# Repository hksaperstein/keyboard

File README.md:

# keyboard
Creating a custom mechanical keyboard pcb with rgbw backlighting

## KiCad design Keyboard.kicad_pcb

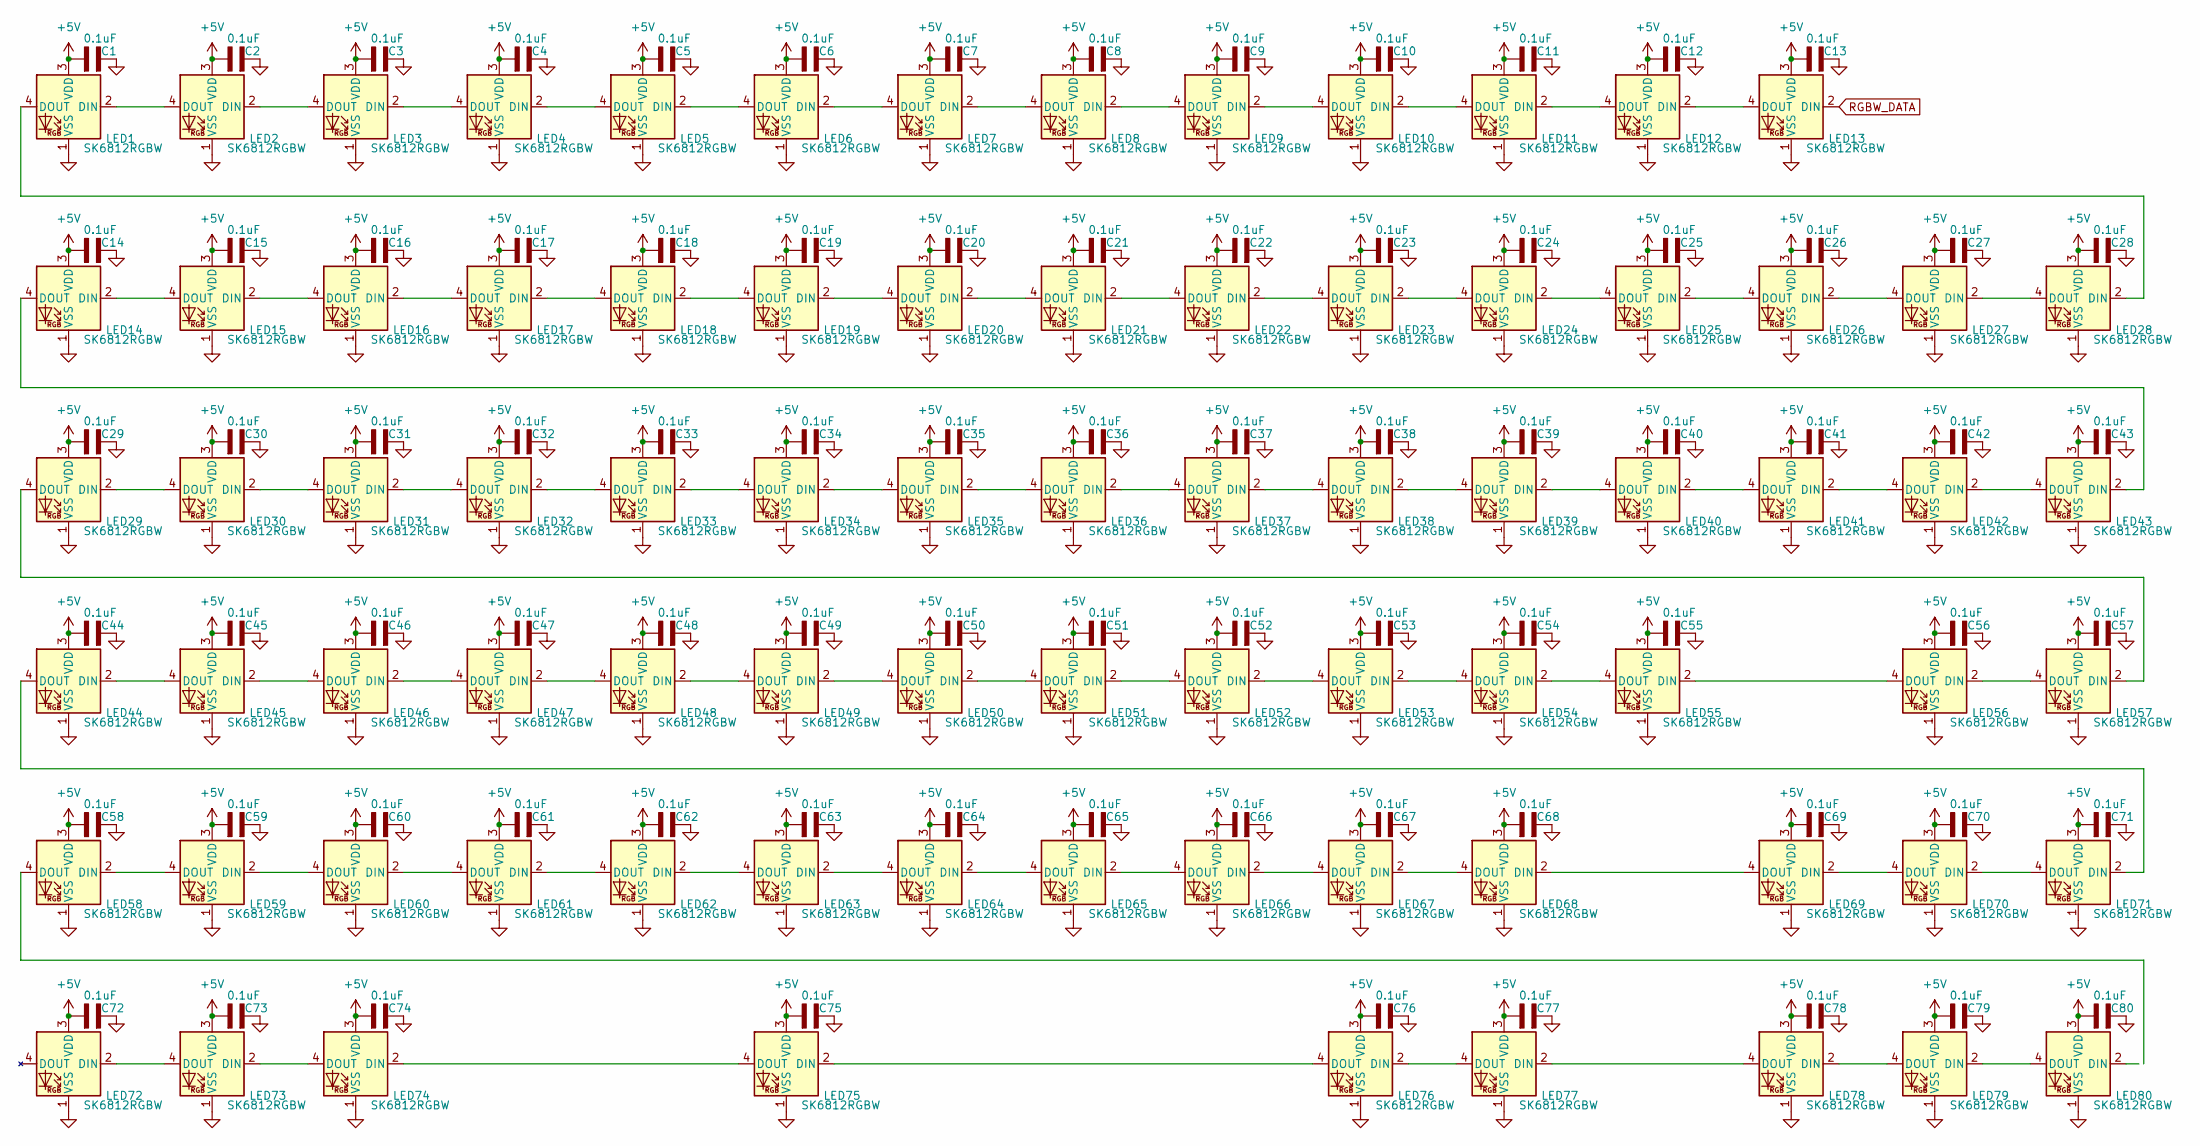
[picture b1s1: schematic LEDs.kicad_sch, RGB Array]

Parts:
C1, C2, C3, C4, C5, C6, C7, C8, C9, C10, C11, C12, C13, C14, C15, C16, C17, C18, C19, C20, C21, C22, C23, C24, C25, C26, C27, C28, C29, C30, C31, C32, C33, C34, C35, C36, C37, C38, C39, C40, C41, C42, C43, C44, C45, C46, C47, C48, C49, C50, C51, C52, C53, C54, C55, C56, C57, C58, C59, C60, C61, C62, C63, C64, C65, C66, C67, C68, C69, C70, C71, C72, C73, C74, C75, C76, C77, C78, C79, C80: 0.1uF; CAPC1608X87N
LED1, LED2, LED3, LED4, LED5, LED6, LED7, LED8, LED9, LED10, LED11, LED12, LED13, LED14, LED15, LED16, LED17, LED18, LED19, LED20, LED21, LED22, LED23, LED24, LED25, LED26, LED27, LED28, LED29, LED30, LED31, LED32, LED33, LED34, LED35, LED36, LED37, LED38, LED39, LED40, LED41, LED42, LED43, LED44, LED45, LED46, LED47, LED48, LED49, LED50, LED51, LED52, LED53, LED54, LED55, LED56, LED57, LED58, LED59, LED60, LED61, LED62, LED63, LED64, LED65, LED66, LED67, LED68, LED69, LED70, LED71, LED72, LED73, LED74, LED75, LED76, LED77, LED78, LED79, LED80: SK6812RGBW; LED_SK6812_PLCC4_5.0x5.0mm_P1.6mm

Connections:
+5V: C1.1, C2.1, C3.1, C4.1, C5.1, C6.1, C7.1, C8.1, C9.1, C10.1, C11.1, C12.1, C13.1, C14.1, C15.1, C16.1, C17.1, C18.1, C19.1, C20.1, C21.1, C22.1, C23.1, C24.1, C25.1, C26.1, C27.1, C28.1, C29.1, C30.1, C31.1, C32.1, C33.1, C34.1, C35.1, C36.1, C37.1, C38.1, C39.1, C40.1, C41.1, C42.1, C43.1, C44.1, C45.1, C46.1, C47.1, C48.1, C49.1, C50.1, C51.1, C52.1, C53.1, C54.1, C55.1, C56.1, C57.1, C58.1, C59.1, C60.1, C61.1, C62.1, C63.1, C64.1, C65.1, C66.1, C67.1, C68.1, C69.1, C70.1, C71.1, C72.1, C73.1, C74.1, C75.1, C76.1, C77.1, C78.1, C79.1, C80.1, LED1.3 (VDD), LED2.3 (VDD), LED3.3 (VDD), LED4.3 (VDD), LED5.3 (VDD), LED6.3 (VDD), LED7.3 (VDD), LED8.3 (VDD), LED9.3 (VDD), LED10.3 (VDD), LED11.3 (VDD), LED12.3 (VDD), LED13.3 (VDD), LED14.3 (VDD), LED15.3 (VDD), LED16.3 (VDD), LED17.3 (VDD), LED18.3 (VDD), LED19.3 (VDD), LED20.3 (VDD), LED21.3 (VDD), LED22.3 (VDD), LED23.3 (VDD), LED24.3 (VDD), LED25.3 (VDD), LED26.3 (VDD), LED27.3 (VDD), LED28.3 (VDD), LED29.3 (VDD), LED30.3 (VDD), LED31.3 (VDD), LED32.3 (VDD), LED33.3 (VDD), LED34.3 (VDD), LED35.3 (VDD), LED36.3 (VDD), LED37.3 (VDD), LED38.3 (VDD), LED39.3 (VDD), LED40.3 (VDD), LED41.3 (VDD), LED42.3 (VDD), LED43.3 (VDD), LED44.3 (VDD), LED45.3 (VDD), LED46.3 (VDD), LED47.3 (VDD), LED48.3 (VDD), LED49.3 (VDD), LED50.3 (VDD), LED51.3 (VDD), LED52.3 (VDD), LED53.3 (VDD), LED54.3 (VDD), LED55.3 (VDD), LED56.3 (VDD), LED57.3 (VDD), LED58.3 (VDD), LED59.3 (VDD), LED60.3 (VDD), LED61.3 (VDD), LED62.3 (VDD), LED63.3 (VDD), LED64.3 (VDD), LED65.3 (VDD), LED66.3 (VDD), LED67.3 (VDD), LED68.3 (VDD), LED69.3 (VDD), LED70.3 (VDD), LED71.3 (VDD), LED72.3 (VDD), LED73.3 (VDD), LED74.3 (VDD), LED75.3 (VDD), LED76.3 (VDD), LED77.3 (VDD), LED78.3 (VDD), LED79.3 (VDD), LED80.3 (VDD)
GND: C1.2, C2.2, C3.2, C4.2, C5.2, C6.2, C7.2, C8.2, C9.2, C10.2, C11.2, C12.2, C13.2, C14.2, C15.2, C16.2, C17.2, C18.2, C19.2, C20.2, C21.2, C22.2, C23.2, C24.2, C25.2, C26.2, C27.2, C28.2, C29.2, C30.2, C31.2, C32.2, C33.2, C34.2, C35.2, C36.2, C37.2, C38.2, C39.2, C40.2, C41.2, C42.2, C43.2, C44.2, C45.2, C46.2, C47.2, C48.2, C49.2, C50.2, C51.2, C52.2, C53.2, C54.2, C55.2, C56.2, C57.2, C58.2, C59.2, C60.2, C61.2, C62.2, C63.2, C64.2, C65.2, C66.2, C67.2, C68.2, C69.2, C70.2, C71.2, C72.2, C73.2, C74.2, C75.2, C76.2, C77.2, C78.2, C79.2, C80.2, LED1.1 (VSS), LED2.1 (VSS), LED3.1 (VSS), LED4.1 (VSS), LED5.1 (VSS), LED6.1 (VSS), LED7.1 (VSS), LED8.1 (VSS), LED9.1 (VSS), LED10.1 (VSS), LED11.1 (VSS), LED12.1 (VSS), LED13.1 (VSS), LED14.1 (VSS), LED15.1 (VSS), LED16.1 (VSS), LED17.1 (VSS), LED18.1 (VSS), LED19.1 (VSS), LED20.1 (VSS), LED21.1 (VSS), LED22.1 (VSS), LED23.1 (VSS), LED24.1 (VSS), LED25.1 (VSS), LED26.1 (VSS), LED27.1 (VSS), LED28.1 (VSS), LED29.1 (VSS), LED30.1 (VSS), LED31.1 (VSS), LED32.1 (VSS), LED33.1 (VSS), LED34.1 (VSS), LED35.1 (VSS), LED36.1 (VSS), LED37.1 (VSS), LED38.1 (VSS), LED39.1 (VSS), LED40.1 (VSS), LED41.1 (VSS), LED42.1 (VSS), LED43.1 (VSS), LED44.1 (VSS), LED45.1 (VSS), LED46.1 (VSS), LED47.1 (VSS), LED48.1 (VSS), LED49.1 (VSS), LED50.1 (VSS), LED51.1 (VSS), LED52.1 (VSS), LED53.1 (VSS), LED54.1 (VSS), LED55.1 (VSS), LED56.1 (VSS), LED57.1 (VSS), LED58.1 (VSS), LED59.1 (VSS), LED60.1 (VSS), LED61.1 (VSS), LED62.1 (VSS), LED63.1 (VSS), LED64.1 (VSS), LED65.1 (VSS), LED66.1 (VSS), LED67.1 (VSS), LED68.1 (VSS), LED69.1 (VSS), LED70.1 (VSS), LED71.1 (VSS), LED72.1 (VSS), LED73.1 (VSS), LED74.1 (VSS), LED75.1 (VSS), LED76.1 (VSS), LED77.1 (VSS), LED78.1 (VSS), LED79.1 (VSS), LED80.1 (VSS)
unnamed: LED1.2 (DIN), LED2.4 (DOUT)
unnamed: LED1.4 (DOUT), LED28.2 (DIN)
unnamed: LED2.2 (DIN), LED3.4 (DOUT)
unnamed: LED3.2 (DIN), LED4.4 (DOUT)
unnamed: LED4.2 (DIN), LED5.4 (DOUT)
unnamed: LED5.2 (DIN), LED6.4 (DOUT)
unnamed: LED6.2 (DIN), LED7.4 (DOUT)
unnamed: LED7.2 (DIN), LED8.4 (DOUT)
unnamed: LED8.2 (DIN), LED9.4 (DOUT)
unnamed: LED10.2 (DIN), LED11.4 (DOUT)
unnamed: LED9.2 (DIN), LED10.4 (DOUT)
unnamed: LED11.2 (DIN), LED12.4 (DOUT)
unnamed: LED12.2 (DIN), LED13.4 (DOUT)
unnamed: LED14.2 (DIN), LED15.4 (DOUT)
unnamed: LED14.4 (DOUT), LED43.2 (DIN)
unnamed: LED15.2 (DIN), LED16.4 (DOUT)
unnamed: LED16.2 (DIN), LED17.4 (DOUT)
unnamed: LED17.2 (DIN), LED18.4 (DOUT)
unnamed: LED18.2 (DIN), LED19.4 (DOUT)
unnamed: LED19.2 (DIN), LED20.4 (DOUT)
unnamed: LED20.2 (DIN), LED21.4 (DOUT)
unnamed: LED21.2 (DIN), LED22.4 (DOUT)
unnamed: LED22.2 (DIN), LED23.4 (DOUT)
unnamed: LED23.2 (DIN), LED24.4 (DOUT)
unnamed: LED24.2 (DIN), LED25.4 (DOUT)
unnamed: LED25.2 (DIN), LED26.4 (DOUT)
unnamed: LED26.2 (DIN), LED27.4 (DOUT)
unnamed: LED27.2 (DIN), LED28.4 (DOUT)
unnamed: LED29.2 (DIN), LED30.4 (DOUT)
unnamed: LED29.4 (DOUT), LED57.2 (DIN)
unnamed: LED30.2 (DIN), LED31.4 (DOUT)
unnamed: LED31.2 (DIN), LED32.4 (DOUT)
unnamed: LED32.2 (DIN), LED33.4 (DOUT)
unnamed: LED33.2 (DIN), LED34.4 (DOUT)
unnamed: LED34.2 (DIN), LED35.4 (DOUT)
unnamed: LED35.2 (DIN), LED36.4 (DOUT)
unnamed: LED36.2 (DIN), LED37.4 (DOUT)
unnamed: LED37.2 (DIN), LED38.4 (DOUT)
unnamed: LED38.2 (DIN), LED39.4 (DOUT)
unnamed: LED39.2 (DIN), LED40.4 (DOUT)
unnamed: LED40.2 (DIN), LED41.4 (DOUT)
unnamed: LED41.2 (DIN), LED42.4 (DOUT)
unnamed: LED42.2 (DIN), LED43.4 (DOUT)
unnamed: LED44.2 (DIN), LED45.4 (DOUT)
unnamed: LED44.4 (DOUT), LED71.2 (DIN)
unnamed: LED45.2 (DIN), LED46.4 (DOUT)
unnamed: LED46.2 (DIN), LED47.4 (DOUT)
unnamed: LED47.2 (DIN), LED48.4 (DOUT)
unnamed: LED48.2 (DIN), LED49.4 (DOUT)
unnamed: LED49.2 (DIN), LED50.4 (DOUT)
unnamed: LED50.2 (DIN), LED51.4 (DOUT)
unnamed: LED51.2 (DIN), LED52.4 (DOUT)
unnamed: LED52.2 (DIN), LED53.4 (DOUT)
unnamed: LED53.2 (DIN), LED54.4 (DOUT)
unnamed: LED54.2 (DIN), LED55.4 (DOUT)
unnamed: LED55.2 (DIN), LED56.4 (DOUT)
unnamed: LED56.2 (DIN), LED57.4 (DOUT)
unnamed: LED58.2 (DIN), LED59.4 (DOUT)
unnamed: LED59.2 (DIN), LED60.4 (DOUT)
unnamed: LED60.2 (DIN), LED61.4 (DOUT)
unnamed: LED61.2 (DIN), LED62.4 (DOUT)
unnamed: LED62.2 (DIN), LED63.4 (DOUT)
unnamed: LED63.2 (DIN), LED64.4 (DOUT)
unnamed: LED64.2 (DIN), LED65.4 (DOUT)
unnamed: LED65.2 (DIN), LED66.4 (DOUT)
unnamed: LED66.2 (DIN), LED67.4 (DOUT)
unnamed: LED67.2 (DIN), LED68.4 (DOUT)
unnamed: LED68.2 (DIN), LED69.4 (DOUT)
unnamed: LED69.2 (DIN), LED70.4 (DOUT)
unnamed: LED70.2 (DIN), LED71.4 (DOUT)
unnamed: LED72.2 (DIN), LED73.4 (DOUT)
unnamed: LED73.2 (DIN), LED74.4 (DOUT)
unnamed: LED74.2 (DIN), LED75.4 (DOUT)
unnamed: LED75.2 (DIN), LED76.4 (DOUT)
unnamed: LED76.2 (DIN), LED77.4 (DOUT)
unnamed: LED77.2 (DIN), LED78.4 (DOUT)
unnamed: LED78.2 (DIN), LED79.4 (DOUT)
unnamed: LED79.2 (DIN), LED80.4 (DOUT)
RGBW_DATA: LED13.2 (DIN)

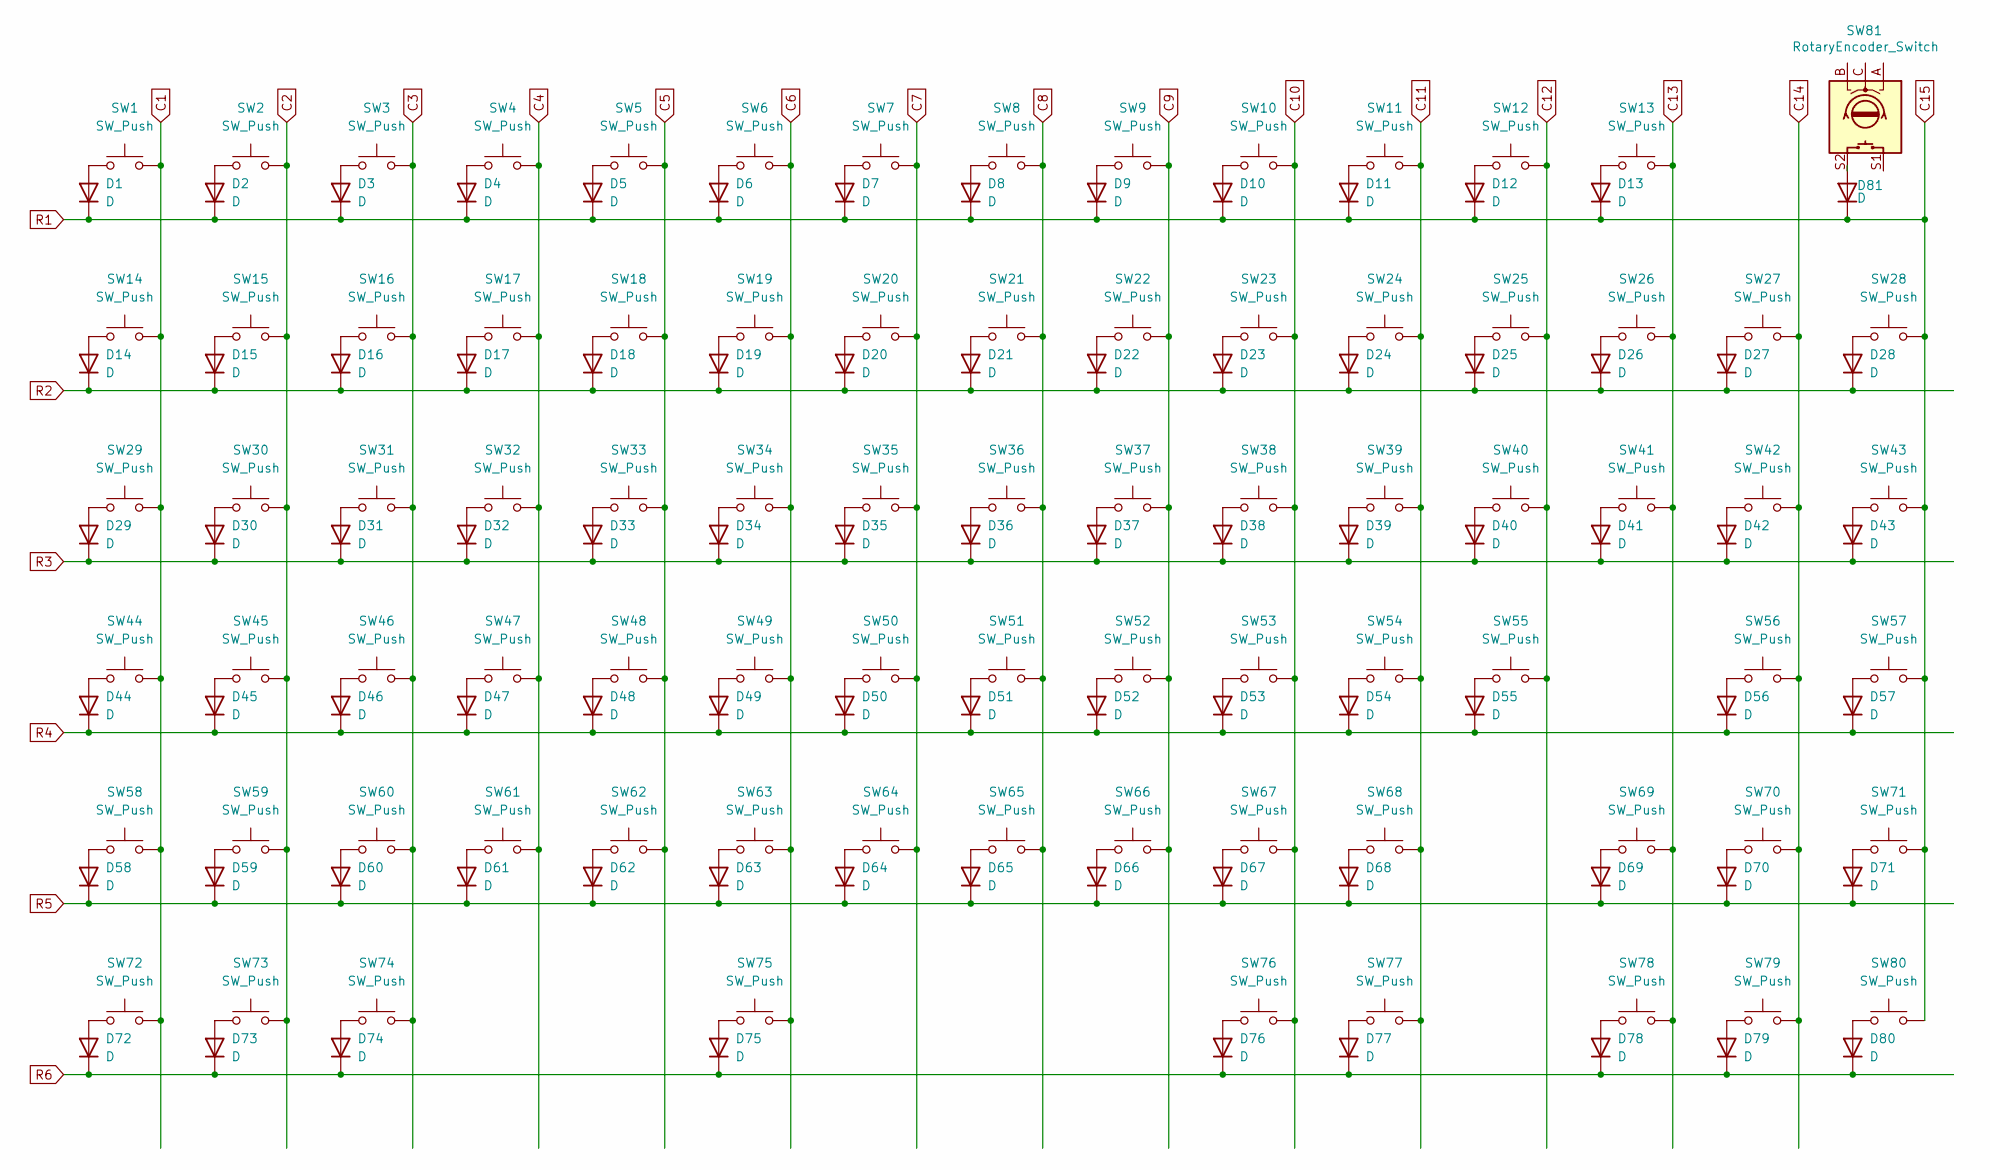
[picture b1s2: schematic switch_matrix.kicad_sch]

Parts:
D1, D2, D3, D4, D5, D6, D7, D8, D9, D10, D11, D12, D13, D14, D15, D16, D17, D18, D19, D20, D21, D22, D23, D24, D25, D26, D27, D28, D29, D30, D31, D32, D33, D34, D35, D36, D37, D38, D39, D40, D41, D42, D43, D44, D45, D46, D47, D48, D49, D50, D51, D52, D53, D54, D55, D56, D57, D58, D59, D60, D61, D62, D63, D64, D65, D66, D67, D68, D69, D70, D71, D72, D73, D74, D75, D76, D77, D78, D79, D80, D81: D; Diode_SOD-123
SW1, SW2, SW3, SW4, SW5, SW6, SW7, SW8, SW9, SW10, SW11, SW12, SW13, SW14, SW15, SW16, SW17, SW18, SW19, SW20, SW21, SW22, SW23, SW24, SW25, SW26, SW28, SW30, SW31, SW32, SW33, SW34, SW35, SW36, SW37, SW38, SW39, SW40, SW41, SW43, SW45, SW46, SW47, SW48, SW49, SW50, SW51, SW52, SW53, SW54, SW55, SW57, SW59, SW60, SW61, SW62, SW63, SW64, SW65, SW66, SW67, SW68, SW70, SW71, SW78, SW79, SW80: SW_Push; Hotswap_MX_1.00u
SW27: SW_Push; Hotswap_MX_2.00u
SW29, SW42: SW_Push; Hotswap_MX_1.50u
SW44, SW69: SW_Push; Hotswap_MX_1.75u
SW56, SW58: SW_Push; Hotswap_MX_2.25u
SW72, SW73, SW74, SW76, SW77: SW_Push; Hotswap_MX_1.25u
SW75: SW_Push; Hotswap_MX_6.25u
SW81: RotaryEncoder_Switch; RotaryEncoder_Alps_EC11E-Switch_Vertical_H20mm

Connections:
C1: SW1.2, SW14.2, SW29.2, SW44.2, SW58.2, SW72.2
C2: SW2.2, SW15.2, SW30.2, SW45.2, SW59.2, SW73.2
C3: SW3.2, SW16.2, SW31.2, SW46.2, SW60.2, SW74.2
C4: SW4.2, SW17.2, SW32.2, SW47.2, SW61.2
C5: SW5.2, SW18.2, SW33.2, SW48.2, SW62.2
C6: SW6.2, SW19.2, SW34.2, SW49.2, SW63.2, SW75.2
C7: SW7.2, SW20.2, SW35.2, SW50.2, SW64.2
C8: SW8.2, SW21.2, SW36.2, SW51.2, SW65.2
C9: SW9.2, SW22.2, SW37.2, SW52.2, SW66.2
C10: SW10.2, SW23.2, SW38.2, SW53.2, SW67.2, SW76.2
C11: SW11.2, SW24.2, SW39.2, SW54.2, SW68.2, SW77.2
C12: SW12.2, SW25.2, SW40.2, SW55.2
C13: SW13.2, SW26.2, SW41.2, SW69.2, SW78.2
C14: SW27.2, SW42.2, SW56.2, SW70.2, SW79.2
unnamed: D1.2 (A), SW1.1
unnamed: D2.2 (A), SW2.1
unnamed: D3.2 (A), SW3.1
unnamed: D4.2 (A), SW4.1
unnamed: D5.2 (A), SW5.1
unnamed: D6.2 (A), SW6.1
unnamed: D7.2 (A), SW7.1
unnamed: D8.2 (A), SW8.1
unnamed: D9.2 (A), SW9.1
unnamed: D10.2 (A), SW10.1
unnamed: D11.2 (A), SW11.1
unnamed: D12.2 (A), SW12.1
unnamed: D13.2 (A), SW13.1
unnamed: D14.2 (A), SW14.1
unnamed: D15.2 (A), SW15.1
unnamed: D16.2 (A), SW16.1
unnamed: D17.2 (A), SW17.1
unnamed: D18.2 (A), SW18.1
unnamed: D19.2 (A), SW19.1
unnamed: D20.2 (A), SW20.1
unnamed: D21.2 (A), SW21.1
unnamed: D22.2 (A), SW22.1
unnamed: D23.2 (A), SW23.1
unnamed: D24.2 (A), SW24.1
unnamed: D25.2 (A), SW25.1
unnamed: D26.2 (A), SW26.1
unnamed: D27.2 (A), SW27.1
unnamed: D28.2 (A), SW28.1
unnamed: D29.2 (A), SW29.1
unnamed: D30.2 (A), SW30.1
unnamed: D31.2 (A), SW31.1
unnamed: D32.2 (A), SW32.1
unnamed: D33.2 (A), SW33.1
unnamed: D34.2 (A), SW34.1
unnamed: D35.2 (A), SW35.1
unnamed: D36.2 (A), SW36.1
unnamed: D37.2 (A), SW37.1
unnamed: D38.2 (A), SW38.1
unnamed: D39.2 (A), SW39.1
unnamed: D40.2 (A), SW40.1
unnamed: D41.2 (A), SW41.1
unnamed: D42.2 (A), SW42.1
unnamed: D43.2 (A), SW43.1
unnamed: D44.2 (A), SW44.1
unnamed: D45.2 (A), SW45.1
unnamed: D46.2 (A), SW46.1
unnamed: D47.2 (A), SW47.1
unnamed: D48.2 (A), SW48.1
unnamed: D49.2 (A), SW49.1
unnamed: D50.2 (A), SW50.1
unnamed: D51.2 (A), SW51.1
unnamed: D52.2 (A), SW52.1
unnamed: D53.2 (A), SW53.1
unnamed: D54.2 (A), SW54.1
unnamed: D55.2 (A), SW55.1
unnamed: D56.2 (A), SW56.1
unnamed: D57.2 (A), SW57.1
unnamed: D58.2 (A), SW58.1
unnamed: D59.2 (A), SW59.1
unnamed: D60.2 (A), SW60.1
unnamed: D61.2 (A), SW61.1
unnamed: D62.2 (A), SW62.1
unnamed: D63.2 (A), SW63.1
unnamed: D64.2 (A), SW64.1
unnamed: D65.2 (A), SW65.1
unnamed: D66.2 (A), SW66.1
unnamed: D67.2 (A), SW67.1
unnamed: D68.2 (A), SW68.1
unnamed: D69.2 (A), SW69.1
unnamed: D70.2 (A), SW70.1
unnamed: D71.2 (A), SW71.1
unnamed: D72.2 (A), SW72.1
unnamed: D73.2 (A), SW73.1
unnamed: D74.2 (A), SW74.1
unnamed: D75.2 (A), SW75.1
unnamed: D76.2 (A), SW76.1
unnamed: D77.2 (A), SW77.1
unnamed: D78.2 (A), SW78.1
unnamed: D79.2 (A), SW79.1
unnamed: D80.2 (A), SW80.1
unnamed: D81.2 (A), SW81.S2
R2: D14.1 (K), D15.1 (K), D16.1 (K), D17.1 (K), D18.1 (K), D19.1 (K), D20.1 (K), D21.1 (K), D22.1 (K), D23.1 (K), D24.1 (K), D25.1 (K), D26.1 (K), D27.1 (K), D28.1 (K)
R3: D29.1 (K), D30.1 (K), D31.1 (K), D32.1 (K), D33.1 (K), D34.1 (K), D35.1 (K), D36.1 (K), D37.1 (K), D38.1 (K), D39.1 (K), D40.1 (K), D41.1 (K), D42.1 (K), D43.1 (K)
R4: D44.1 (K), D45.1 (K), D46.1 (K), D47.1 (K), D48.1 (K), D49.1 (K), D50.1 (K), D51.1 (K), D52.1 (K), D53.1 (K), D54.1 (K), D55.1 (K), D56.1 (K), D57.1 (K)
R5: D58.1 (K), D59.1 (K), D60.1 (K), D61.1 (K), D62.1 (K), D63.1 (K), D64.1 (K), D65.1 (K), D66.1 (K), D67.1 (K), D68.1 (K), D69.1 (K), D70.1 (K), D71.1 (K)
R6: D72.1 (K), D73.1 (K), D74.1 (K), D75.1 (K), D76.1 (K), D77.1 (K), D78.1 (K), D79.1 (K), D80.1 (K)

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
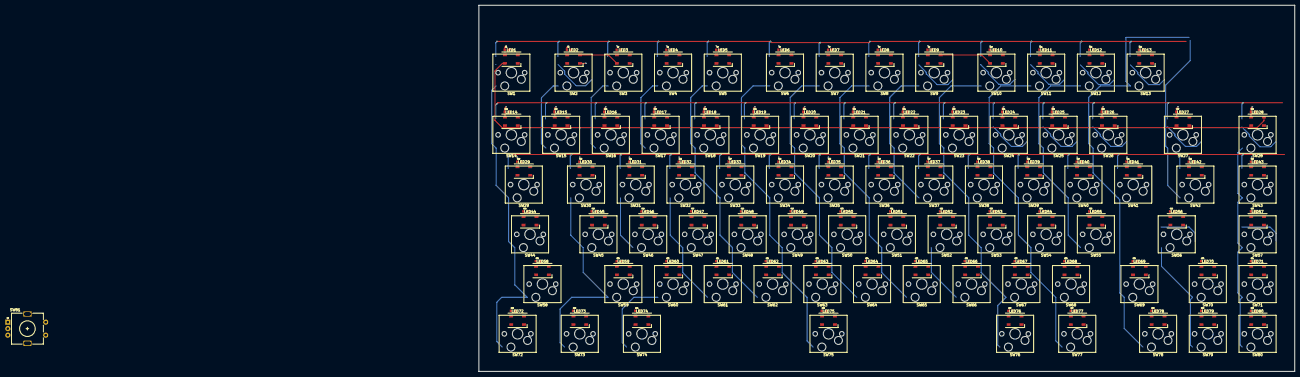
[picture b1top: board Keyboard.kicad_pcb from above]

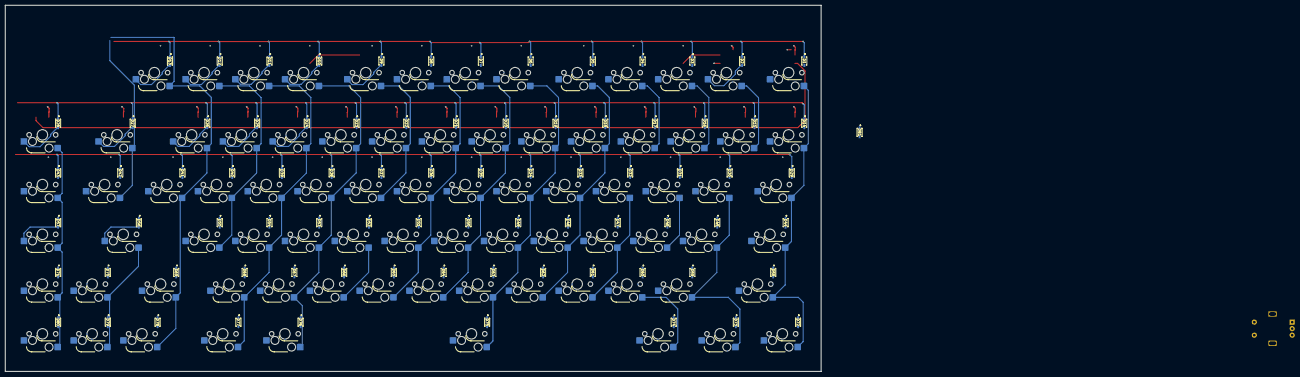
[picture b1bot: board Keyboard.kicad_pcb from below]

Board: 4 copper layers, 312.4 x 140.2 mm, 322 parts (81 on the bottom side), 182 nets.

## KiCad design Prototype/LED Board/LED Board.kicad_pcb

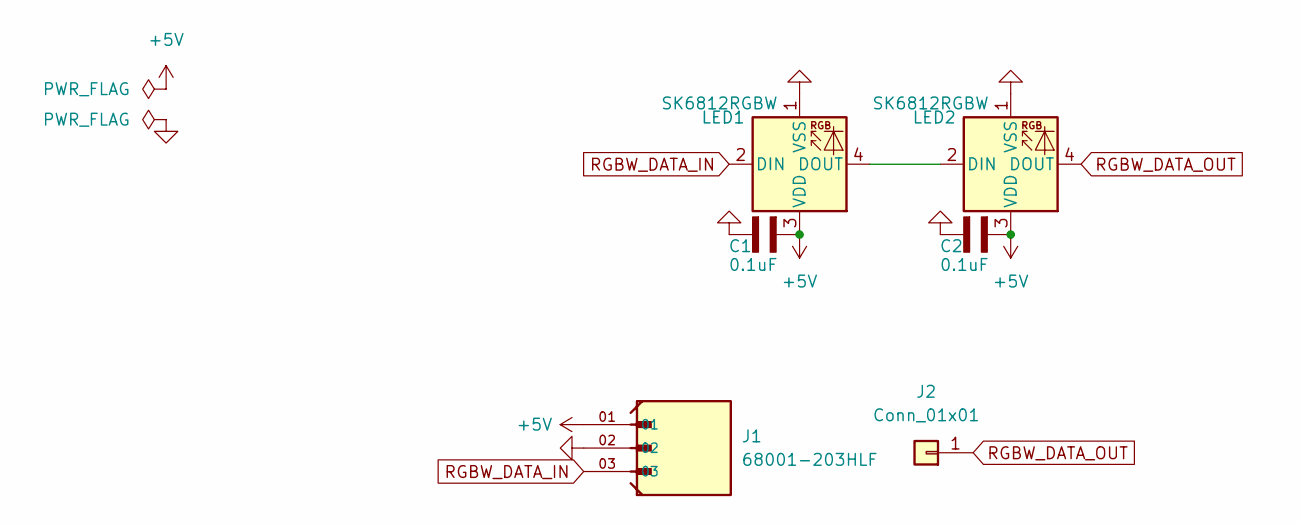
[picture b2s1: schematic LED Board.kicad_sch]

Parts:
C1, C2: 0.1uF; CAPC1608X87N
J1: 68001-203HLF; AMPHENOL_68001-203HLF; PARTREV DF
J2: Conn_01x01; PinSocket_1x01_P2.54mm_Horizontal
LED1, LED2: SK6812RGBW; LED_SK6812_PLCC4_5.0x5.0mm_P1.6mm

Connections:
+5V: C1.1, C2.1, J1.01, LED1.3 (VDD), LED2.3 (VDD)
GND: C1.2, C2.2, J1.02, LED1.1 (VSS), LED2.1 (VSS)
unnamed: LED1.4 (DOUT), LED2.2 (DIN)
RGBW_DATA_IN: J1.03, LED1.2 (DIN)
RGBW_DATA_OUT: J2.1, LED2.4 (DOUT)

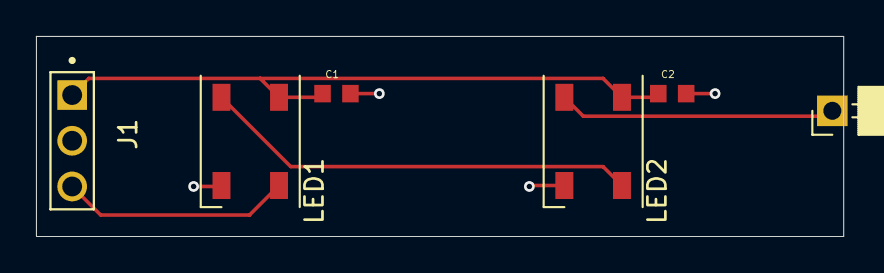
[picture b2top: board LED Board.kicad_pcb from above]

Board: 2 copper layers, 44.8 x 11.1 mm, 6 parts (0 on the bottom side), 5 nets.

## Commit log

2024-12-01 added .gitignore
2024-12-01 updated .gitignore
2024-12-06 switch matrix schem, layout of switchs and diodes, rgb array schem
2024-12-07 updated BOM library
2024-12-08 auto layout of pcb including rgbw/caps
2024-12-09 updated footprint with cap alignment
2024-12-19 Start of keyboard site
2024-12-20 change to jekyll
2024-12-20 added jekyll files
2024-12-20 update jekyll theme
2024-12-20 update theme syntax
2024-12-20 update site title/description
2024-12-20 Added jekyll minimal-mistakes theme
2024-12-31 Created BOM and added parts. Created v0.1 prototype 2x2
2025-01-21 work on v0.3 of prototype board, new mounting holes/trace runs
2025-01-28 figuring out website
2025-01-30 site restart
2025-01-30 added theme
2025-01-30 basic functionality working
2025-01-31 started home page, started first post
2025-01-31 added navigation and collection pages
